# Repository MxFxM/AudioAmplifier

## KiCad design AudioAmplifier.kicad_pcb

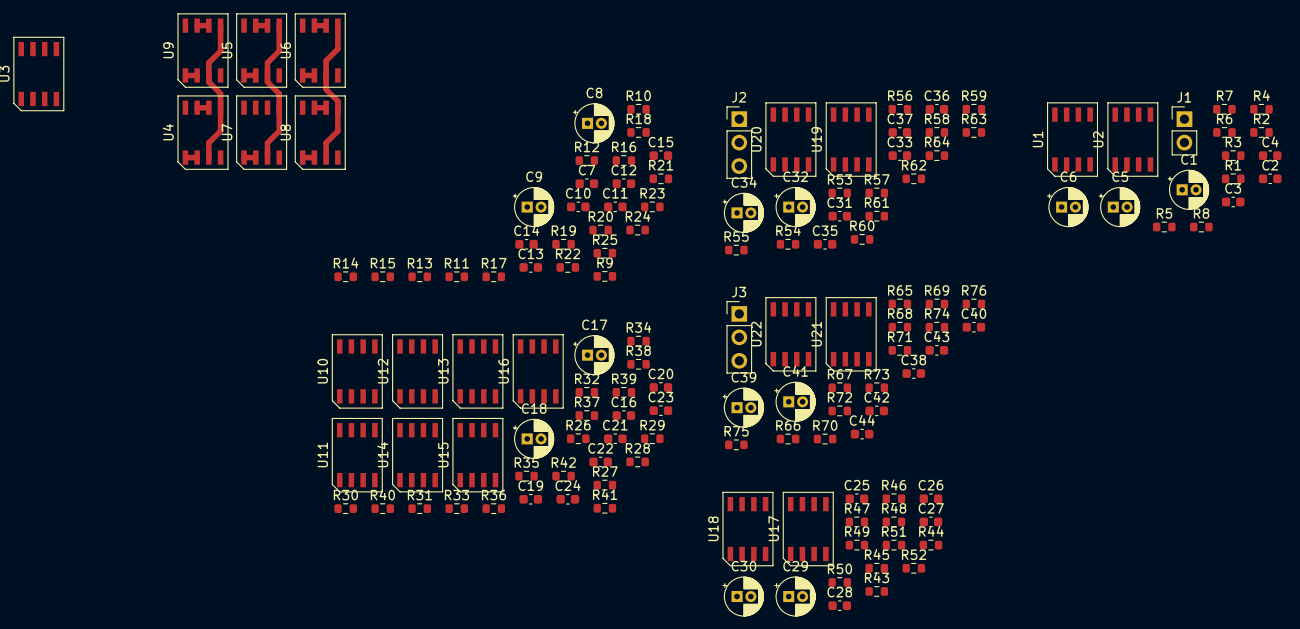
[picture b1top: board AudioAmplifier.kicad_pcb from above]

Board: 2 copper layers, 145 parts (0 on the bottom side), 86 nets.

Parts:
C1, C5, C6, C8, C17, C34, C41: 10u; CP_Radial_D4.0mm_P1.50mm
C2, C3, C4, C7, C10, C11, C12, C13, C14, C15, C16, C19, C20, C21, C22, C23, C24, C25, C26, C31, C33, C38, C40: 100n; C_0603_1608Metric
C9, C18: 2200u; CP_Radial_D4.0mm_P1.50mm
C27, C28: 1n; C_0603_1608Metric
C29, C30: 4u7; CP_Radial_D4.0mm_P1.50mm
C32, C39: 220u; CP_Radial_D4.0mm_P1.50mm
C35, C36, C42, C43: 100p; C_0603_1608Metric
C37, C44: 470p; C_0603_1608Metric
J1: Conn_01x02; PinHeader_1x02_P2.54mm_Vertical
J2, J3: Conn_01x03; PinHeader_1x03_P2.54mm_Vertical
R1, R2, R3, R4: 2k2; R_0603_1608Metric
R5, R6, R7, R8, R10, R12, R13, R27, R29, R30, R49, R50, R51, R52, R60, R61, R72, R73: 10R; R_0603_1608Metric
R9, R11, R26, R28: 10k; R_0603_1608Metric
R14, R15, R16, R17, R18, R19, R20, R21, R22, R23, R24, R25, R31, R32, R33, R34, R35, R36, R37, R38, R39, R40, R41, R42: 1R; R_0603_1608Metric
R43, R44: 100R; R_0603_1608Metric
R45, R46, R47, R48: 22k; R_0603_1608Metric
R53, R65: 47k; R_0603_1608Metric
R54, R55, R56, R57, R63, R66, R67, R68, R69, R75: 1k; R_0603_1608Metric
R58, R59, R70, R71: 5k6; R_0603_1608Metric
R62, R64, R74, R76: 3k3; R_0603_1608Metric
U1, U2, U3, U4, U5, U6, U7, U8, U9, U10, U11, U12, U13, U14, U15, U16, U17, U18, U19, U20, U21, U22: LMH6658; LMH6658MAX

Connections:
+12V: C1.1, C2.1, C3.1, C4.1, C7.1, C10.1, C11.1, C12.1, C13.1, C14.1, C15.1, C16.1, C19.1, C20.1, C21.1, C22.1, C23.1, C24.1, C25.1, C26.1, C31.1, C33.1, C38.1, C40.1, J1.2, R1.1, R3.1, U1.8, U2.8, U3.8, U4.8, U5.8, U6.8, U7.8, U8.8, U9.8, U10.8, U11.8, U12.8, U13.8, U14.8, U15.8, U16.8, U17.8, U18.8, U19.8, U20.8, U21.8, U22.8
BUFFER_IN_LEFT: R12.1, R13.1, U4.3, U4.5, U5.3, U5.5, U6.3, U6.5, U7.3, U7.5, U8.3, U8.5, U9.3, U9.5
BUFFER_IN_RIGHT: R29.1, R30.1, U11.3, U11.5, U12.3, U12.5, U13.3, U13.5, U14.3, U14.5, U15.3, U15.5, U16.3, U16.5
BUFFER_OUT_LEFT: R10.2, R14.1, R15.1, R16.1, R17.1, R18.1, R19.1, R20.1, R21.1, R22.1, R23.1, R24.1, R25.1
BUFFER_OUT_RIGHT: R27.2, R31.1, R32.1, R33.1, R34.1, R35.1, R36.1, R37.1, R38.1, R39.1, R40.1, R41.1, R42.1
GND: C1.2, C2.2, C3.2, C4.2, C5.2, C6.2, C7.2, C10.2, C11.2, C12.2, C13.2, C14.2, C15.2, C16.2, C19.2, C20.2, C21.2, C22.2, C23.2, C24.2, C25.2, C26.2, C27.2, C28.2, C31.2, C33.2, C38.2, C40.2, J1.1, R2.2, R4.2, R11.2, R28.2, R45.2, R46.2, U1.4, U2.4, U3.4, U4.4, U5.4, U6.4, U7.4, U8.4, U9.4, U10.4, U11.4, U12.4, U13.4, U14.4, U15.4, U16.4, U17.4, U18.4, U19.4, U20.4, U21.4, U22.4
unnamed: C5.1, R1.2, R2.1, U1.3, U1.5
unnamed: C6.1, R3.2, R4.1, U2.3, U2.5
unnamed: C8.1, R9.2, U3.3, U3.5
unnamed: C9.2, R10.1
unnamed: C17.1, R26.2, U10.3, U10.5
unnamed: C18.2, R27.1
unnamed: C27.1, C29.2, R43.1, R45.1
unnamed: C28.1, C30.2, R44.1, R46.1
unnamed: C29.1, R47.2, U17.3, U17.5
unnamed: C30.1, R48.2, U18.3, U18.5
unnamed: C32.1, J2.1
unnamed: C34.1, J2.2
unnamed: C34.2, R53.1, U20.3
unnamed: C35.1, R58.1, R60.2, U19.1
unnamed: C35.2, R55.1, R58.2, U19.2
unnamed: C36.1, R59.1, R61.2, U19.7
unnamed: C36.2, R57.1, R59.2, U19.6
unnamed: C37.2, R62.1, R64.2, U20.6
unnamed: C39.1, J3.1
unnamed: C41.1, J3.2
unnamed: C41.2, R65.1, U21.3
unnamed: C42.1, R70.1, R72.2, U22.1
unnamed: C42.2, R67.1, R70.2, U22.2
unnamed: C43.1, R71.1, R73.2, U21.7
unnamed: C43.2, R69.1, R71.2, U21.6
unnamed: C44.2, R74.1, R76.2, U22.6
unnamed: J2.3, R60.1, R61.1, R62.2
unnamed: J3.3, R72.1, R73.1, R74.2
unnamed: R5.2, U1.1, U1.2
unnamed: R6.2, U1.6, U1.7
unnamed: R7.2, U2.1, U2.2
unnamed: R8.2, U2.6, U2.7
unnamed: R12.2, U3.1, U3.2
unnamed: R13.2, U3.6, U3.7
unnamed: R14.2, U4.1, U4.2
unnamed: R15.2, U4.6, U4.7
unnamed: R16.2, U5.1, U5.2
unnamed: R17.2, U5.6, U5.7
unnamed: R18.2, U6.1, U6.2
unnamed: R19.2, U6.6, U6.7
unnamed: R20.2, U7.1, U7.2
unnamed: R21.2, U7.6, U7.7
unnamed: R22.2, U8.1, U8.2
unnamed: R23.2, U8.6, U8.7
unnamed: R24.2, U9.1, U9.2
unnamed: R25.2, U9.6, U9.7
unnamed: R29.2, U10.1, U10.2
unnamed: R30.2, U10.6, U10.7
unnamed: R31.2, U11.1, U11.2
unnamed: R32.2, U11.6, U11.7
unnamed: R33.2, U12.1, U12.2
unnamed: R34.2, U12.6, U12.7
unnamed: R35.2, U13.1, U13.2
unnamed: R36.2, U13.6, U13.7
unnamed: R37.2, U14.1, U14.2
unnamed: R38.2, U14.6, U14.7
unnamed: R39.2, U15.1, U15.2
unnamed: R40.2, U15.6, U15.7
unnamed: R41.2, U16.1, U16.2
unnamed: R42.2, U16.6, U16.7
unnamed: R49.2, U17.1, U17.2
unnamed: R50.2, U17.6, U17.7
unnamed: R51.2, U18.1, U18.2
unnamed: R52.2, U18.6, U18.7
unnamed: R54.1, U19.3
unnamed: R55.2, R57.2, U20.1, U20.2
unnamed: R56.1, U19.5
unnamed: R63.1, U20.5
unnamed: R66.1, U22.3
unnamed: R67.2, R69.2, U21.1, U21.2
unnamed: R68.1, U21.5
unnamed: R75.1, U22.5
POWER_OUT_LEFT: C9.1, R11.1
POWER_OUT_RIGHT: C18.1, R28.1
VAS_IN_LEFT: C32.2, R51.1, R52.1
VAS_IN_RIGHT: C39.2, R49.1, R50.1
VAS_OUT_LEFT: C8.2, C37.1, R64.1, U20.7
VAS_OUT_RIGHT: C17.2, C44.1, R76.1, U22.7
VBIAS_LEFT: R5.1, R6.1, R9.1, R48.1, R53.2, R54.2, R56.2, R63.2
VBIAS_RIGHT: R7.1, R8.1, R26.1, R47.1, R65.2, R66.2, R68.2, R75.2
